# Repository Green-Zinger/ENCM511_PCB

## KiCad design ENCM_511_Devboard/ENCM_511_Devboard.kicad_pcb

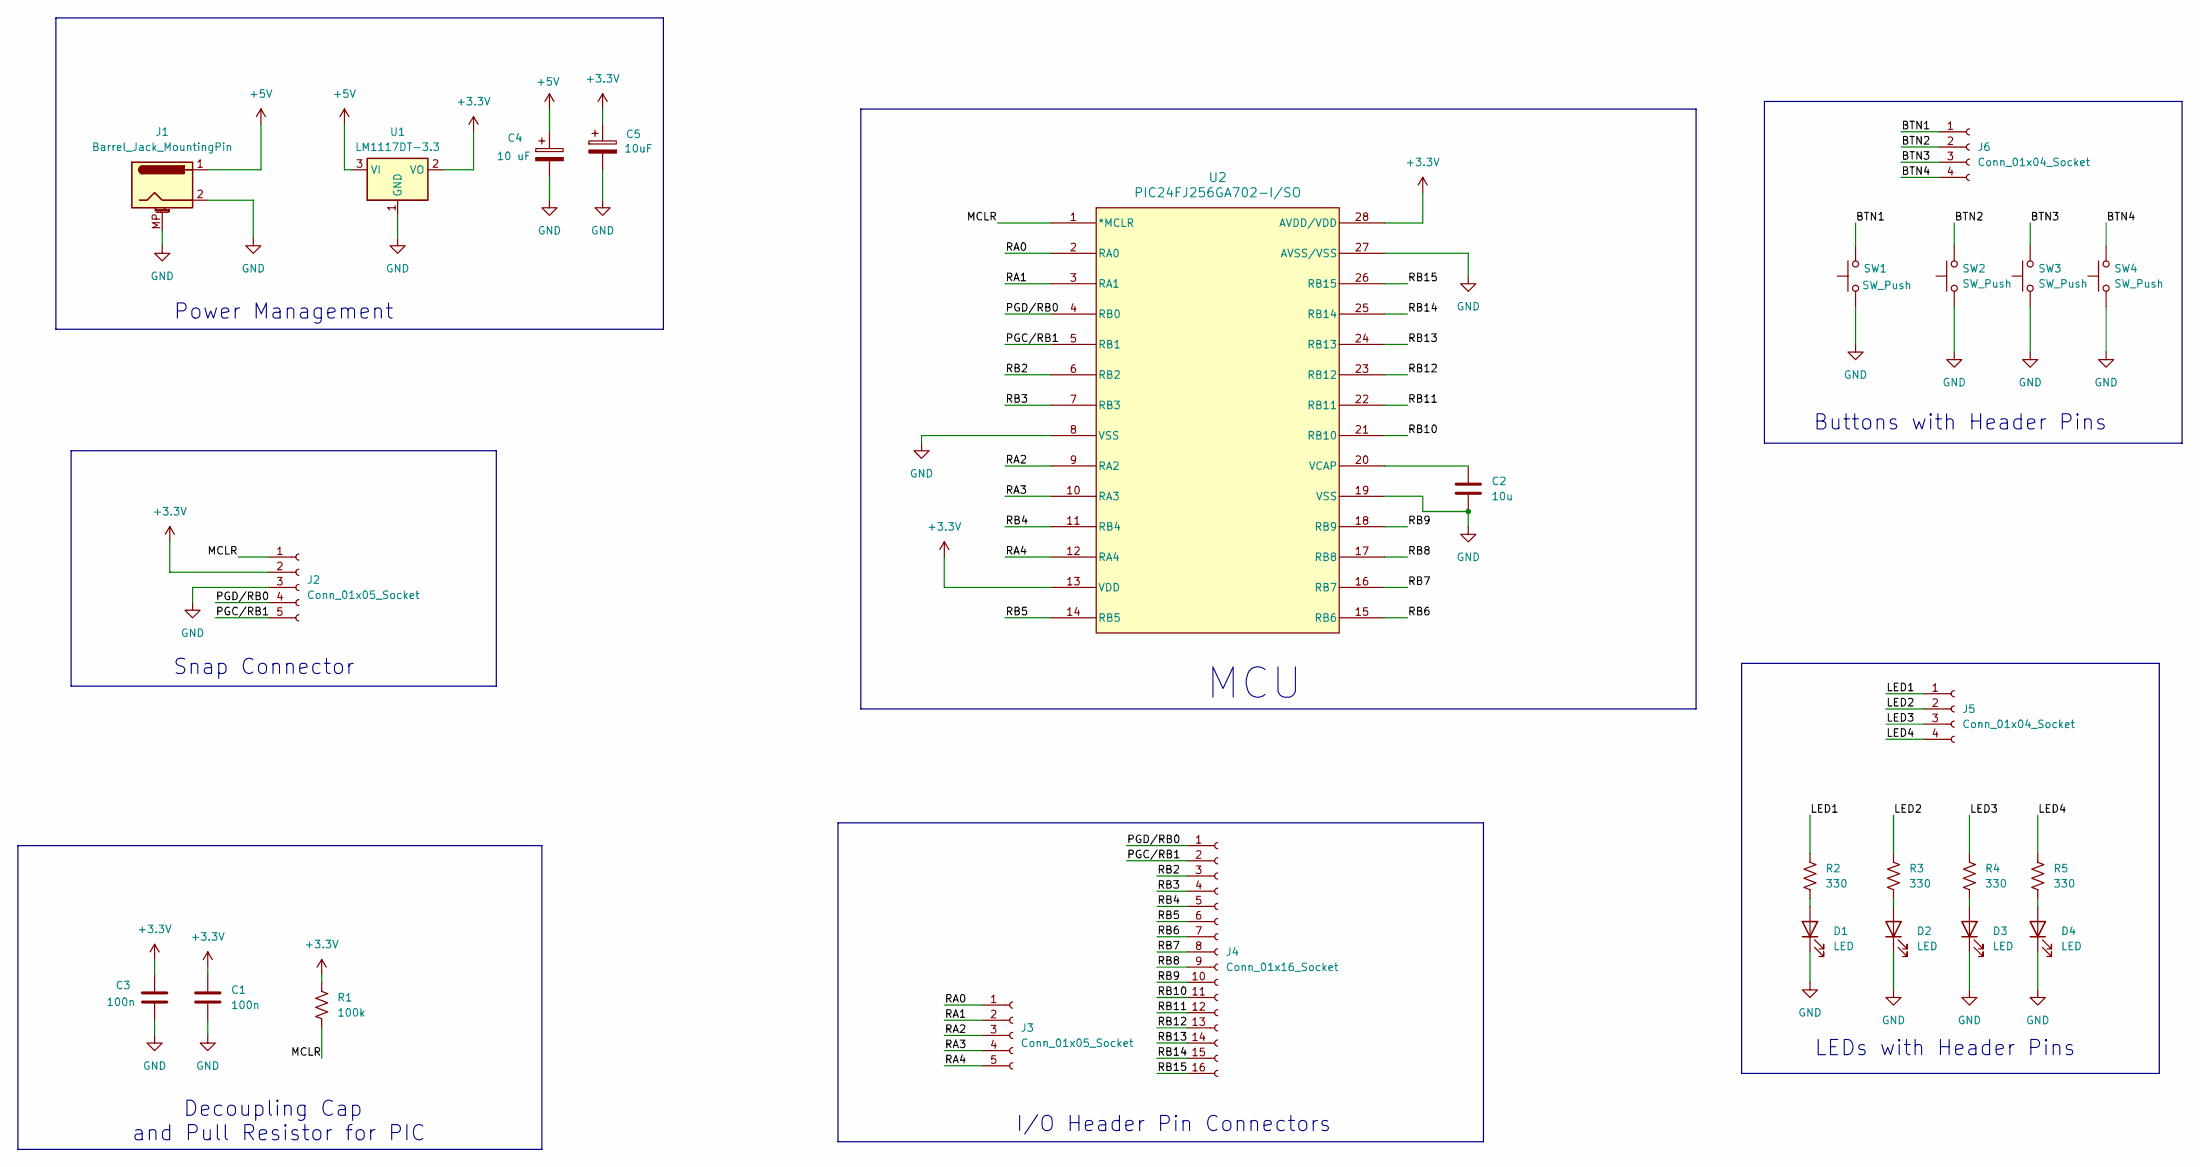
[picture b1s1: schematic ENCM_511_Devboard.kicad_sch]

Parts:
C1, C3: 100n; C_1206_3216Metric_Pad1.33x1.80mm_HandSolder
C2: 10u; C_1206_3216Metric_Pad1.33x1.80mm_HandSolder
C4: 10 uF; C_1206_3216Metric_Pad1.33x1.80mm_HandSolder
C5: 10uF; C_1206_3216Metric_Pad1.33x1.80mm_HandSolder
D1, D2, D3, D4: LED; LED_1206_3216Metric_Pad1.42x1.75mm_HandSolder
J1: Barrel_Jack_MountingPin; BarrelJack_Horizontal_personal
J2, J3: Conn_01x05_Socket; PinSocket_1x05_P2.54mm_Vertical
J4: Conn_01x16_Socket; PinSocket_1x16_P2.54mm_Vertical
J5, J6: Conn_01x04_Socket; PinSocket_1x04_P2.54mm_Vertical
R1: 100k; R_1206_3216Metric_Pad1.30x1.75mm_HandSolder
R2, R3, R4, R5: 330; R_1206_3216Metric_Pad1.30x1.75mm_HandSolder
SW1, SW2, SW3, SW4: SW_Push; SW_PUSH_6mm
U1: LM1117DT-3.3; TO-252-3_TabPin2
U2: PIC24FJ256GA702-I/SO; SOIC28_SO_MCH

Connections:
+3.3V: C1.1, C3.1, C5.1, J2.2, R1.1, U1.2 (VO), U2.13 (VDD), U2.28 (AVDD/VDD)
+5V: C4.1, J1.1, U1.3 (VI)
/BTN1: J6.1, SW1.2
/BTN2: J6.2, SW2.2
/BTN3: J6.3, SW3.2
/BTN4: J6.4, SW4.2
/LED1: J5.1, R2.1
/LED2: J5.2, R3.1
/LED3: J5.3, R4.1
/LED4: J5.4, R5.1
/MCLR: J2.1, R1.2, U2.1 (*MCLR)
/PGC/RB1: J2.5, J4.2, U2.5 (RB1)
/PGD/RB0: J2.4, J4.1, U2.4 (RB0)
/RA0: J3.1, U2.2 (RA0)
/RA1: J3.2, U2.3 (RA1)
/RA2: J3.3, U2.9 (RA2)
/RA3: J3.4, U2.10 (RA3)
/RA4: J3.5, U2.12 (RA4)
/RB2: J4.3, U2.6 (RB2)
/RB3: J4.4, U2.7 (RB3)
/RB4: J4.5, U2.11 (RB4)
/RB5: J4.6, U2.14 (RB5)
/RB6: J4.7, U2.15 (RB6)
/RB7: J4.8, U2.16 (RB7)
/RB8: J4.9, U2.17 (RB8)
/RB9: J4.10, U2.18 (RB9)
/RB10: J4.11, U2.21 (RB10)
/RB11: J4.12, U2.22 (RB11)
/RB12: J4.13, U2.23 (RB12)
/RB13: J4.14, U2.24 (RB13)
/RB14: J4.15, U2.25 (RB14)
/RB15: J4.16, U2.26 (RB15)
GND: C1.2, C2.2, C3.2, C4.2, C5.2, D1.1 (K), D2.1 (K), D3.1 (K), D4.1 (K), J1.2, J1.MP (MountPin_MP), J2.3, SW1.1, SW2.1, SW3.1, SW4.1, U1.1 (GND), U2.8 (VSS), U2.19 (VSS), U2.27 (AVSS/VSS)
unnamed: D1.2 (A), R2.2
unnamed: D2.2 (A), R3.2
unnamed: D3.2 (A), R4.2
unnamed: D4.2 (A), R5.2
unnamed: C2.1, U2.20 (VCAP)

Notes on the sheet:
I/O Header Pin Connectors
Snap Connector
LEDs with Header Pins
MCU
Decoupling Cap and Pull Resistor for PIC
Buttons with Header Pins
Power Management

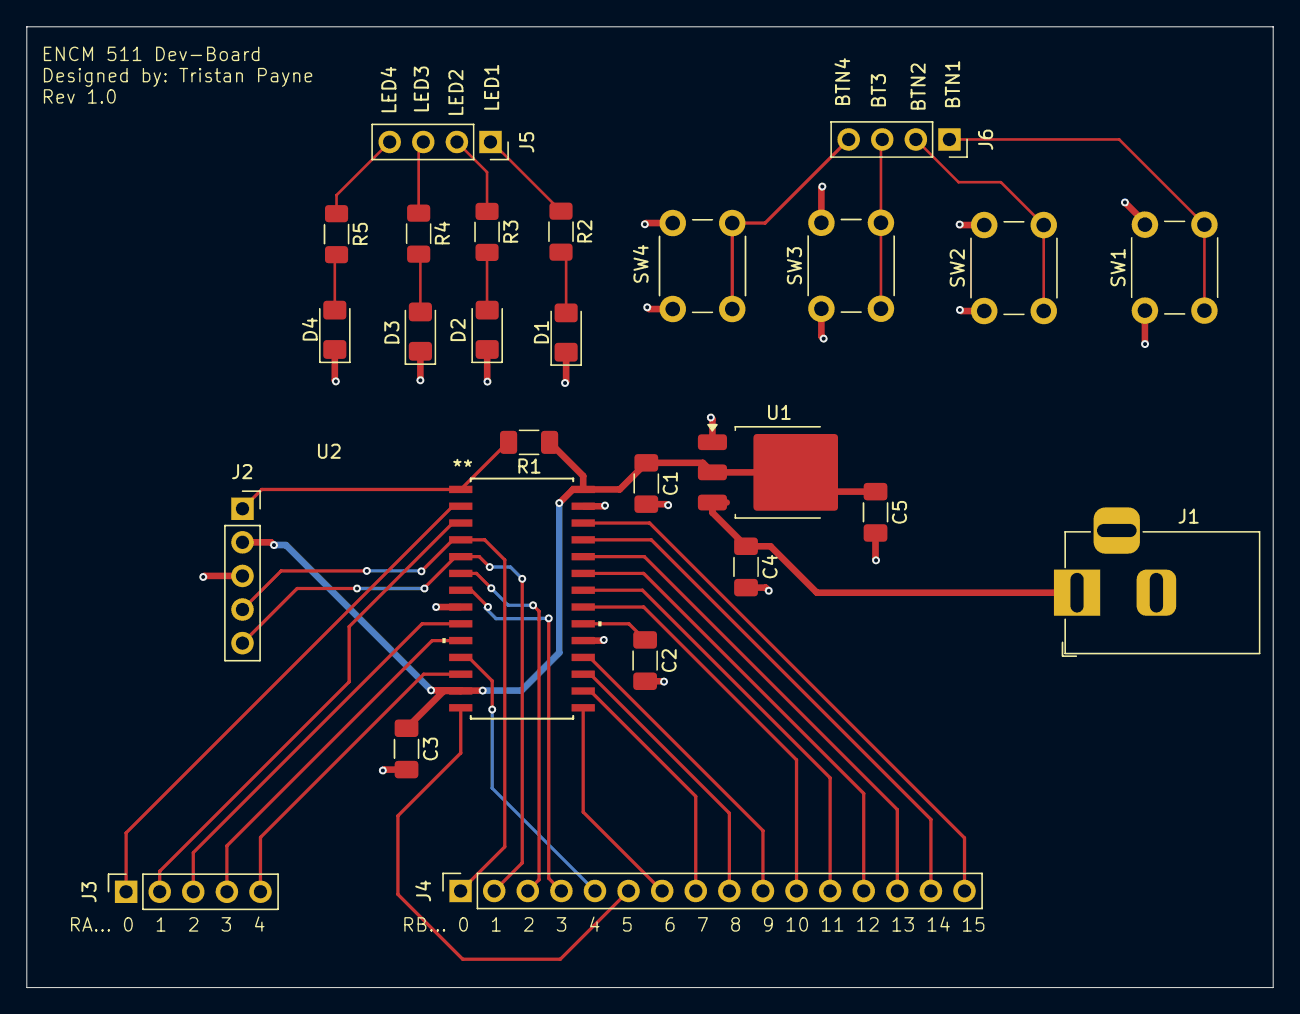
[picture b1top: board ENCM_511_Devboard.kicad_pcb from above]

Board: 2 copper layers, 94.2 x 72.6 mm, 26 parts (0 on the bottom side), 38 nets.

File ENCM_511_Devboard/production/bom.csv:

Designator,Footprint,Quantity,Value,LCSC Part #
"C1, C3",1206,2,100n,
C2,1206,1,10u,
"C4, C5",1206,2,C_Polarized,
"D1, D2, D3, D4",1206,4,LED,
J1,BarrelJack_Horizontal_personal,1,Barrel_Jack_MountingPin,
"J2, J3",PinSocket_1x05_P2.54mm_Vertical,2,Conn_01x05_Socket,
J4,PinSocket_1x16_P2.54mm_Vertical,1,Conn_01x16_Socket,
"J5, J6",PinSocket_1x04_P2.54mm_Vertical,2,Conn_01x04_Socket,
R1,1206,1,100k,
"R2, R3, R4, R5",1206,4,330,
"SW1, SW2, SW3, SW4",SW_PUSH_6mm,4,SW_Push,
U1,TO-252-3_TabPin2,1,LM1117DT-3.3,
U2,SOIC28_SO_MCH,1,PIC24FJ256GA702-I/SO,
